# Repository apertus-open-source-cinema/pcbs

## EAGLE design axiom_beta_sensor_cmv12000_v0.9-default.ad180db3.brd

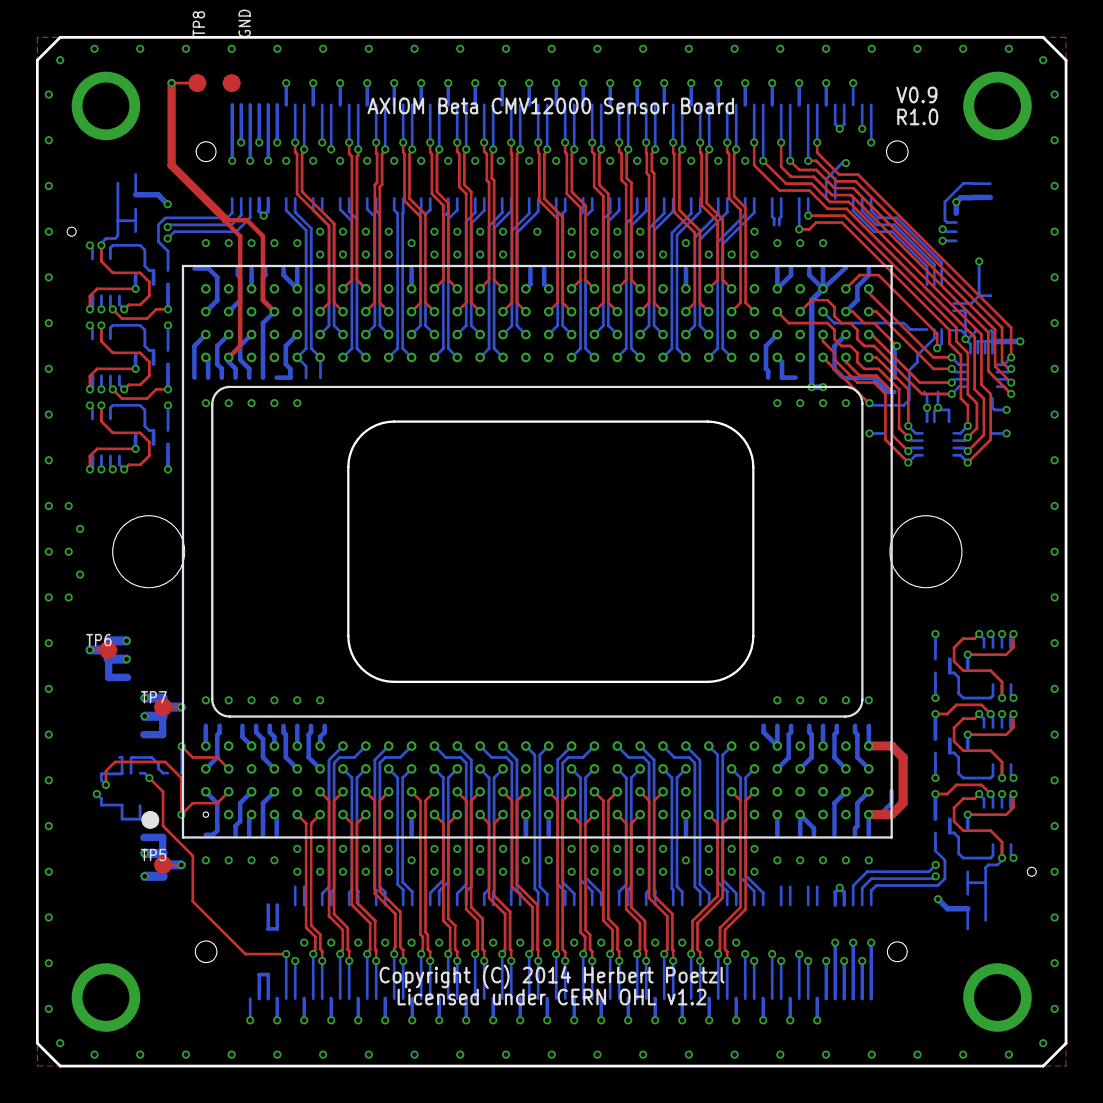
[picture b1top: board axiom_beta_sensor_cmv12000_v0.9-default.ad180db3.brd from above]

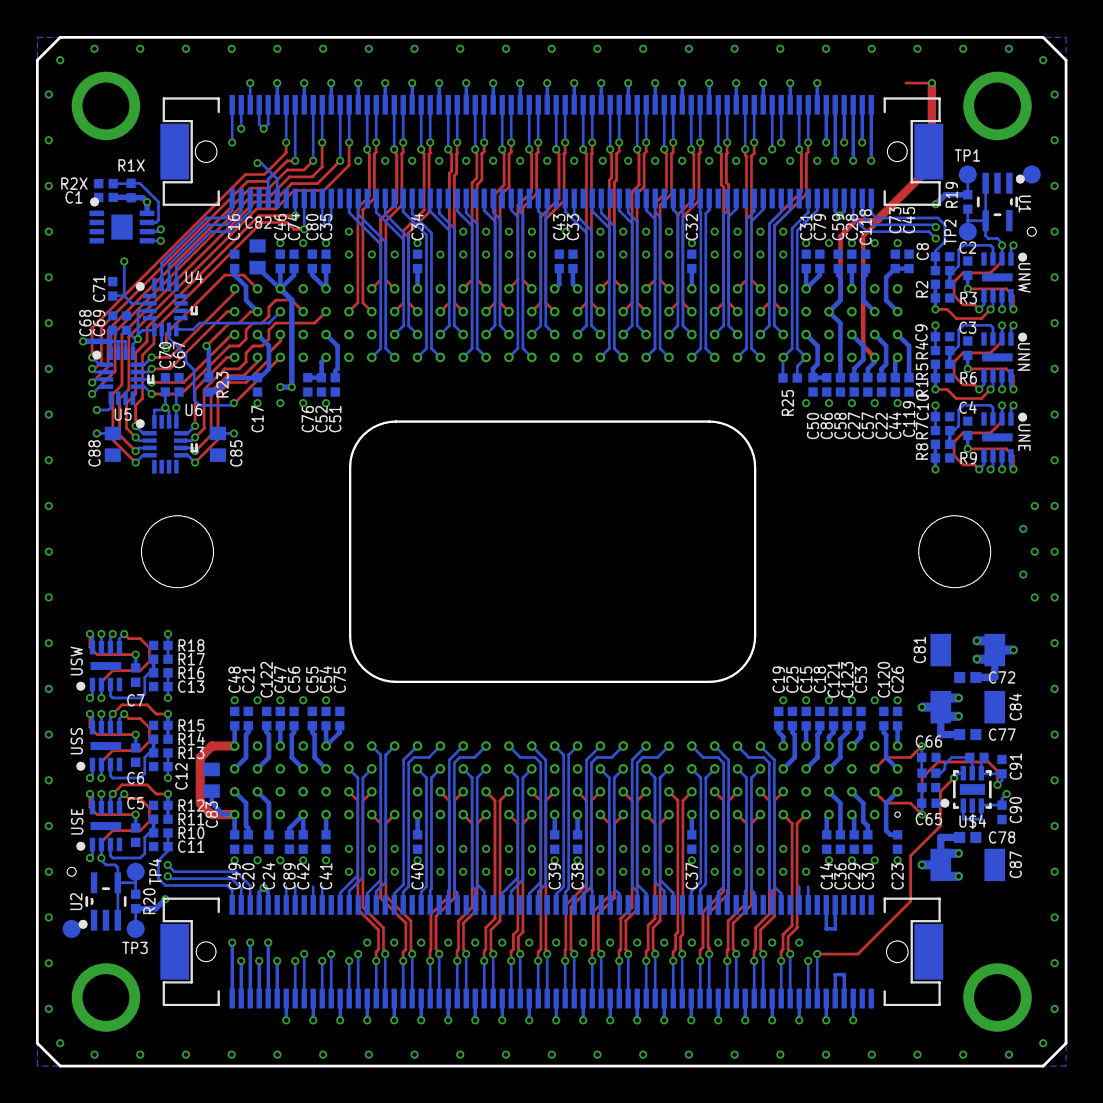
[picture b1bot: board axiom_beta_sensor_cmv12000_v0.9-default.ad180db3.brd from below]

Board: 4 copper layers, 57.1 x 57.1 mm, 148 parts (140 on the bottom side), 231 nets.

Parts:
C1, C2, C3, C4, C5, C6, C7, C14, C15, C16, C17, C18, C19, C20, C21, C22, C23, C24, C25, C26, C27, C28, C29, C30, C31, C32, C33, C34, C35, C36, C37, C38, C39, C40, C41, C42, C43, C44, C45, C46, C47, C48, C49, C50, C51, C52, C53, C54, C55, C56, C57, C58, C65, C66, C67, C68, C69, C70, C71, C118, C119, C120, C121, C122, C123: 100n; 0402-C
C8, C9, C10, C11, C12, C13: 1µ; 0402-C
C59, C73, C74, C75, C76, C79, C80, C86, C89, C90, C91: 4µ7; 0402-C
C72, C77, C78: 4µ7; 0402-B
C81, C84, C87: 100µ; 1206-B
C82, C83, C85, C88: 10µ; 0603-C
GND, GND75, GND77: TPTP10R; TP10R
PARALLELLA: PARALLELLA-FRAME
R1, R1X, R2, R2X, R3, R4, R5, R6, R7, R8, R9, R10, R11, R12, R13, R14, R15, R16, R17, R18, R19, R20, R21, R22, R23, R24, R25: 0402-C
TP1, TP2, TP3, TP4, TP5, TP6, TP7, TP8: TPTP10R; TP10R
U1, U2: TLV431ACDCKR; SOT65P210X110-5N
U4: SN74AVC4T245RSV; QFN40P185X265X55-16N
U5, U6: SN74AVC4T774RSV; QFN40P185X265X55-16N
U$1: µZ-FRAME
U$2: CMV12000ANDON; 10-30-07-237-400T4
U$4: MIC47050; MLF-6
UEP: BR24G04NUX; DFN200X300X100-9N
UNE: TS332IQ2T; DFN200X200X100-9N
UNN: TS332IQ2T; DFN200X200X100-9N
UNW: TS332IQ2T; DFN200X200X100-9N
USE: TS332IQ2T; DFN200X200X100-9N
USS: TS332IQ2T; DFN200X200X100-9N
USW: TS332IQ2T; DFN200X200X100-9N
X-NORTH: FX10-144P; FX10A-144P
X-SOUTH: FX10-144P; FX10A-144P

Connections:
CLK_IN: U6.12, U$2.E30
FRAME_REQ: U5.11, U$2.G30
GND: C1.2, C2.2, C3.2, C4.2, C5.2, C6.2, C7.2, C8.2, C9.2, C10.2, C11.2, C12.2, C13.2, C14.2, C15.2, C16.2, C17.2, C18.2, C19.2, C20.2, C21.2, C22.1, C23.1, C24.1, C25.1, C26.1, C27.1, C28.1, C29.2, C30.2, C31.2, C32.2, C33.2, C34.2, C35.2, C36.2, C37.2, C38.2, C39.2, C40.2, C41.2, C42.2, C43.2, C44.2, C45.2, C46.2, C47.2, C48.2, C49.2, C50.2, C51.2, C52.2, C53.2, C54.2, C55.2, C56.2, C57.2, C58.2, C59.2, C65.2, C66.2, C67.2, C68.2, C69.2, C70.2, C71.2, C72.2, C73.2, C74.2, C75.2, C76.2, C77.2, C78.2, C79.2, C80.2, C81.2, C82.2, C83.2, C84.2, C85.2, C86.2, C87.2, C88.2, C89.2, C90.2, C91.1, C118.2, C119.2, C120.2, C121.2, C122.2, C123.2, GND.TP, GND75.TP, GND77.TP, R2X.2, R3.2, R6.2, R9.2, R12.2, R15.2, R18.2, R22.1, U1.5, U2.5, U4.1, U4.4, U4.9, U4.10, U4.11, U4.16, U5.6, U5.7, U5.8, U6.5, U6.6, U6.7, U6.8, U6.15, U$2.A9, U$2.A21, U$2.A25, U$2.A28, U$2.A29, U$2.B5, U$2.B22, U$2.B26, U$2.B27, U$2.B28, U$2.C15, U$2.C16, U$2.C28, U$2.D2, U$2.D25, U$2.D27, U$2.D29, U$2.E3, U$2.E15, U$2.E16, U$2.E25, U$2.E27, U$2.F27, U$2.G5, U$2.H1, U$2.H6, U$2.H9, U$2.H21, U$2.H25, U$2.H27, U$4.2, U$4.EP, UEP.1, UEP.2, UEP.3, UEP.4, UEP.EP, UNE.4, UNE.EP, UNN.4, UNN.EP, UNW.4, UNW.EP, USE.4, USE.EP, USS.4, USS.EP, USW.4, USW.EP, X-NORTH.12, X-NORTH.18, X-NORTH.24, X-NORTH.30, X-NORTH.36, X-NORTH.42, X-NORTH.48, X-NORTH.54, X-NORTH.60, X-NORTH.66, X-NORTH.72, X-NORTH.78, X-NORTH.84, X-NORTH.90, X-NORTH.96, X-NORTH.102, X-NORTH.108, X-NORTH.114, X-NORTH.120, X-NORTH.126, X-NORTH.132, X-NORTH.138, X-NORTH.139, X-SOUTH.12, X-SOUTH.18, X-SOUTH.24, X-SOUTH.30, X-SOUTH.36, X-SOUTH.42, X-SOUTH.48, X-SOUTH.54, X-SOUTH.60, X-SOUTH.66, X-SOUTH.72, X-SOUTH.78, X-SOUTH.84, X-SOUTH.90, X-SOUTH.96, X-SOUTH.102, X-SOUTH.108, X-SOUTH.114, X-SOUTH.120, X-SOUTH.126, X-SOUTH.132, X-SOUTH.138, X-SOUTH.139
N00_N: R25.2, U$2.E6, X-NORTH.16
N00_P: R25.1, U$2.E5, X-NORTH.14
N01_N: U$2.G7, X-NORTH.17
N01_P: U$2.G6, X-NORTH.15
N02_N: U$2.F7, X-NORTH.22
N02_P: U$2.F6, X-NORTH.20
N04_N: U$2.E8, X-NORTH.28
N04_P: U$2.E7, X-NORTH.26
N05_N: U$2.H8, X-NORTH.29
N05_P: U$2.H7, X-NORTH.27
N06_N: U$2.F9, X-NORTH.34
N06_P: U$2.F8, X-NORTH.32
N07_N: U$2.G9, X-NORTH.35
N07_P: U$2.G8, X-NORTH.33
N08_N: U$2.E10, X-NORTH.40
N08_P: U$2.E9, X-NORTH.38
N09_N: U$2.G11, X-NORTH.41
N09_P: U$2.G10, X-NORTH.39
N10_N: U$2.F11, X-NORTH.46
N10_P: U$2.F10, X-NORTH.44
N11_N: U$2.H12, X-NORTH.47
N11_P: U$2.H11, X-NORTH.45
N12_N: U$2.E12, X-NORTH.52
N12_P: U$2.E11, X-NORTH.50
N13_N: U$2.G13, X-NORTH.53
N13_P: U$2.G12, X-NORTH.51
N14_N: U$2.F13, X-NORTH.58
N14_P: U$2.F12, X-NORTH.56
N15_N: U$2.H14, X-NORTH.59
N15_P: U$2.H13, X-NORTH.57
N16_N: U$2.E14, X-NORTH.64
N16_P: U$2.E13, X-NORTH.62
N17_N: U$2.G15, X-NORTH.65
N17_P: U$2.G14, X-NORTH.63
N18_N: U$2.F15, X-NORTH.70
N18_P: U$2.F14, X-NORTH.68
N19_N: U$2.G17, X-NORTH.71
N19_P: U$2.G16, X-NORTH.69
N20_N: U$2.F17, X-NORTH.76
N20_P: U$2.F16, X-NORTH.74
N21_N: U$2.H18, X-NORTH.77
N21_P: U$2.H17, X-NORTH.75
N22_N: U$2.E18, X-NORTH.82
N22_P: U$2.E17, X-NORTH.80
N23_N: U$2.G19, X-NORTH.83
N23_P: U$2.G18, X-NORTH.81
N24_N: U$2.F19, X-NORTH.88
N24_P: U$2.F18, X-NORTH.86
N25_N: U$2.H20, X-NORTH.89
N25_P: U$2.H19, X-NORTH.87
N26_N: U$2.E20, X-NORTH.94
N26_P: U$2.E19, X-NORTH.92
N27_N: U$2.G21, X-NORTH.95
N27_P: U$2.G20, X-NORTH.93
N28_N: U$2.F21, X-NORTH.100
N28_P: U$2.F20, X-NORTH.98
N29_N: U$2.G23, X-NORTH.101
N29_P: U$2.G22, X-NORTH.99
N30_N: U$2.E22, X-NORTH.106
N30_P: U$2.E21, X-NORTH.104
N31_N: U$2.H24, X-NORTH.107
N31_P: U$2.H23, X-NORTH.105
N32_N: U$2.F23, X-NORTH.112
N32_P: U$2.F22, X-NORTH.110
N33_N: U$2.G25, X-NORTH.113
N33_P: U$2.G24, X-NORTH.111
N34_N: U$2.E24, X-NORTH.118
N34_P: U$2.E23, X-NORTH.116
N35_N: U6.4, X-NORTH.119
N35_P: U6.3, X-NORTH.117
N37_N: U5.3, X-NORTH.125
N37_P: U5.4, X-NORTH.123
N38_N: U6.2, X-NORTH.130
N38_P: U6.1, X-NORTH.128
N39_N: U5.1, X-NORTH.131
N39_P: U5.2, X-NORTH.129
unnamed: R1X.2, R2X.1, UEP.7
unnamed: C118.1, U$2.G2
unnamed: C119.1, U$2.F1
unnamed: C120.1, U$2.C1
unnamed: C121.1, U$2.D4
unnamed: C122.1, U$2.C29
unnamed: C123.1, U$2.C4
unnamed: C14.1, U$2.A4
unnamed: C15.1, U$2.D5
unnamed: R21.1, R22.2, U$4.5
unnamed: C18.1, U$2.C5
unnamed: C19.1, U$2.D6
unnamed: C20.1, U$2.B30
unnamed: C21.1, U$2.C30
unnamed: C22.2, U$2.F2
unnamed: C23.2, U$2.B1
unnamed: C24.2, U$2.B29
unnamed: C25.2, U$2.C6
unnamed: C26.2, U$2.D1
unnamed: C27.2, U$2.F3
unnamed: C28.2, U$2.H3
unnamed: C29.1, U$2.A3
unnamed: C30.1, U$2.B3
unnamed: R11.2, R12.1, USE.6
unnamed: R5.2, R6.1, UNN.6
unnamed: R8.2, R9.1, UNE.6
unnamed: R10.2, R11.1, USE.3
unnamed: R7.2, R8.1, UNE.3
unnamed: R1.2, R2.1, UNW.3
unnamed: R2.2, R3.1, UNW.6
unnamed: R14.2, R15.1, USS.6
unnamed: R13.2, R14.1, USS.3
unnamed: R16.2, R17.1, USW.3
unnamed: R17.2, R18.1, USW.6
N_CHK_V: C2.1, C3.1, C4.1, R19.1, TP1.TP, UNE.8, UNN.8, UNW.8, X-NORTH.8, X-NORTH.10
N_I2C_V: C1.1, R1X.1, UEP.8, X-NORTH.135, X-NORTH.137
N_REF: R19.2, TP2.TP, U1.3, U1.4, UNE.2, UNE.5, UNN.2, UNN.5, UNW.2, UNW.5
N_SCK: U4.15, X-NORTH.144
N_SCL: UEP.6, X-NORTH.143
N_SDA: UEP.5, X-NORTH.141
N_SDI: U4.13, X-NORTH.140
N_SDO: U4.14, X-NORTH.142
N_SPI_V: C71.1, U4.2, X-NORTH.134, X-NORTH.136
N_VE: C50.1, C51.1, C52.1, C53.1, C54.1, C55.1, C56.1, C67.1, C69.1, C75.1, C76.1, C77.1, C84.1, C85.1, C86.1, TP7.TP, U4.3, U4.5, U5.13, U6.13, U$2.C26, U$2.C27, U$2.D3, U$2.D26, U$2.E26, U$2.F5, U$2.F26, X-NORTH.103, X-NORTH.109, X-NORTH.115, X-NORTH.121, X-NORTH.127, X-NORTH.133
N_VE_CV: C10.1, R7.1, X-NORTH.6
N_VE_OV: UNE.7, X-NORTH.5
N_VE_UV: UNE.1, X-NORTH.11
N_VN: C31.1, C32.1, C33.1, C34.1, C35.1, C36.1, C37.1, C38.1, C39.1, C40.1, C41.1, C42.1, C43.1, C44.1, C68.1, C70.1, C78.1, C79.1, C80.1, C87.1, C88.1, C89.1, TP5.TP, U5.5, U5.14, U5.15, U5.16, U6.14, U6.16, U$2.A10, U$2.A15, U$2.A16, U$2.A22, U$2.A26, U$2.A27, U$2.B4, U$2.E1, U$2.H5, U$2.H10, U$2.H15, U$2.H16, U$2.H22, U$2.H26, X-NORTH.49, X-NORTH.55, X-NORTH.61, X-NORTH.67, X-NORTH.73, X-NORTH.79, X-NORTH.85, X-NORTH.91, X-NORTH.97
N_VN_CV: C9.1, R4.1, X-NORTH.4
N_VN_OV: UNN.7, X-NORTH.3
N_VN_UV: UNN.1, X-NORTH.9
N_VW: C57.1, C58.1, C59.1, TP8.TP, U$2.E2, U$2.G4, X-NORTH.13, X-NORTH.19, X-NORTH.25, X-NORTH.31, X-NORTH.37, X-NORTH.43
N_VW_CV: C8.1, R1.1, X-NORTH.2
N_VW_OV: UNW.7, X-NORTH.1
N_VW_UV: UNW.1, X-NORTH.7
R5: R4.2, R5.1, UNN.3
S04_N: U$2.C24, X-SOUTH.28
S04_P: U$2.C25, X-SOUTH.26
S06_N: U$2.D23, X-SOUTH.34
S06_P: U$2.D24, X-SOUTH.32
S07_N: U$2.B24, X-SOUTH.35
S07_P: U$2.B25, X-SOUTH.33
S08_N: U$2.D21, X-SOUTH.40
S08_P: U$2.D22, X-SOUTH.38
S09_N: U$2.A23, X-SOUTH.41
S09_P: U$2.A24, X-SOUTH.39
S10_N: U$2.C21, X-SOUTH.46
S10_P: U$2.C22, X-SOUTH.44
S11_N: U$2.B20, X-SOUTH.47
S11_P: U$2.B21, X-SOUTH.45
S12_N: U$2.D19, X-SOUTH.52
S12_P: U$2.D20, X-SOUTH.50
S13_N: U$2.A19, X-SOUTH.53
S13_P: U$2.A20, X-SOUTH.51
S14_N: U$2.C19, X-SOUTH.58
S14_P: U$2.C20, X-SOUTH.56
S15_N: U$2.B18, X-SOUTH.59
S15_P: U$2.B19, X-SOUTH.57
S16_N: U$2.C17, X-SOUTH.64
S16_P: U$2.C18, X-SOUTH.62
S17_N: U$2.A17, X-SOUTH.65
S17_P: U$2.A18, X-SOUTH.63
S18_N: U$2.D17, X-SOUTH.70
S18_P: U$2.D18, X-SOUTH.68
S19_N: U$2.B16, X-SOUTH.71
S19_P: U$2.B17, X-SOUTH.69
S20_N: U$2.D15, X-SOUTH.76
S20_P: U$2.D16, X-SOUTH.74
S21_N: U$2.B14, X-SOUTH.77
S21_P: U$2.B15, X-SOUTH.75
S22_N: U$2.D13, X-SOUTH.82
S22_P: U$2.D14, X-SOUTH.80
S23_N: U$2.A13, X-SOUTH.83
S23_P: U$2.A14, X-SOUTH.81
S24_N: U$2.C13, X-SOUTH.88
S24_P: U$2.C14, X-SOUTH.86
S25_N: U$2.B12, X-SOUTH.89
S25_P: U$2.B13, X-SOUTH.87
S26_N: U$2.D11, X-SOUTH.94
S26_P: U$2.D12, X-SOUTH.92
S27_N: U$2.A11, X-SOUTH.95
S27_P: U$2.A12, X-SOUTH.93
S28_N: U$2.C11, X-SOUTH.100
S28_P: U$2.C12, X-SOUTH.98
S29_N: U$2.B10, X-SOUTH.101
S29_P: U$2.B11, X-SOUTH.99
S30_N: U$2.C9, X-SOUTH.106
S30_P: U$2.C10, X-SOUTH.104
S31_N: U$2.B8, X-SOUTH.107
S31_P: U$2.B9, X-SOUTH.105
S32_N: U$2.D9, X-SOUTH.112
S32_P: U$2.D10, X-SOUTH.110
S33_N: U$2.A7, X-SOUTH.113
S33_P: U$2.A8, X-SOUTH.111
S34_N: U$2.C7, X-SOUTH.118
S34_P: U$2.C8, X-SOUTH.116
S35_N: U$2.B6, X-SOUTH.119
S35_P: U$2.B7, X-SOUTH.117
S36_N: U$2.D7, X-SOUTH.124
S36_P: U$2.D8, X-SOUTH.122
S37_N: U$2.A5, X-SOUTH.125
S37_P: U$2.A6, X-SOUTH.123
S39_N: U$4.6, X-SOUTH.131
SPI_CLK: U4.6, U$2.H29
SPI_EN: U6.9, U$2.F28
SPI_IN: U4.7, U$2.E28
SPI_OUT: U4.8, U$2.G28
SYS_RES_N: U5.10, U$2.F30
S_CHK_V: C5.1, C6.1, C7.1, R20.1, TP3.TP, USE.8, USS.8, USW.8, X-SOUTH.8, X-SOUTH.10
S_I2C_V: X-SOUTH.135, X-SOUTH.137
S_REF: R20.2, TP4.TP, U2.3, U2.4, USE.2, USE.5, USS.2, USS.5, USW.2, USW.5
S_SPI_V: X-SOUTH.134, X-SOUTH.136
S_VE: X-SOUTH.13, X-SOUTH.19, X-SOUTH.25, X-SOUTH.31, X-SOUTH.37, X-SOUTH.43
S_VE_CV: C11.1, R10.1, X-SOUTH.2
S_VE_OV: USE.7, X-SOUTH.1
S_VE_UV: USE.1, X-SOUTH.7
S_VS: C45.1, C46.1, C47.1, C48.1, C49.1, C72.1, C73.1, C74.1, C81.1, C82.1, C83.1, TP6.TP, U$2.A30, U$2.D28, U$2.D30, U$2.G1, U$2.H28, X-SOUTH.49, X-SOUTH.55, X-SOUTH.61, X-SOUTH.67, X-SOUTH.73, X-SOUTH.79, X-SOUTH.85, X-SOUTH.91, X-SOUTH.97
S_VS_CV: C12.1, R13.1, X-SOUTH.4
S_VS_OV: USS.7, X-SOUTH.3
S_VS_UV: USS.1, X-SOUTH.9
S_VW: C90.1, U$4.1, U$4.3, X-SOUTH.103, X-SOUTH.109, X-SOUTH.115, X-SOUTH.121, X-SOUTH.127, X-SOUTH.133
S_VW_CV: C13.1, R16.1, X-SOUTH.6
S_VW_OV: USW.7, X-SOUTH.5
S_VW_UV: USW.1, X-SOUTH.11
TDIG1: U5.9, U$2.G27
TDIG2: U6.11, U$2.G26
T_EXP1: U5.12, U$2.H30
T_EXP2: U6.10, U$2.E29
VRAMP1: C16.1, R23.1, U$2.G29
VRAMP2: C17.1, R23.2, U$2.F29
VTREF: C65.1, C91.2, R21.2, R24.1, U$2.B2, U$4.4
VTSIG: C66.1, R24.2, U$2.C2

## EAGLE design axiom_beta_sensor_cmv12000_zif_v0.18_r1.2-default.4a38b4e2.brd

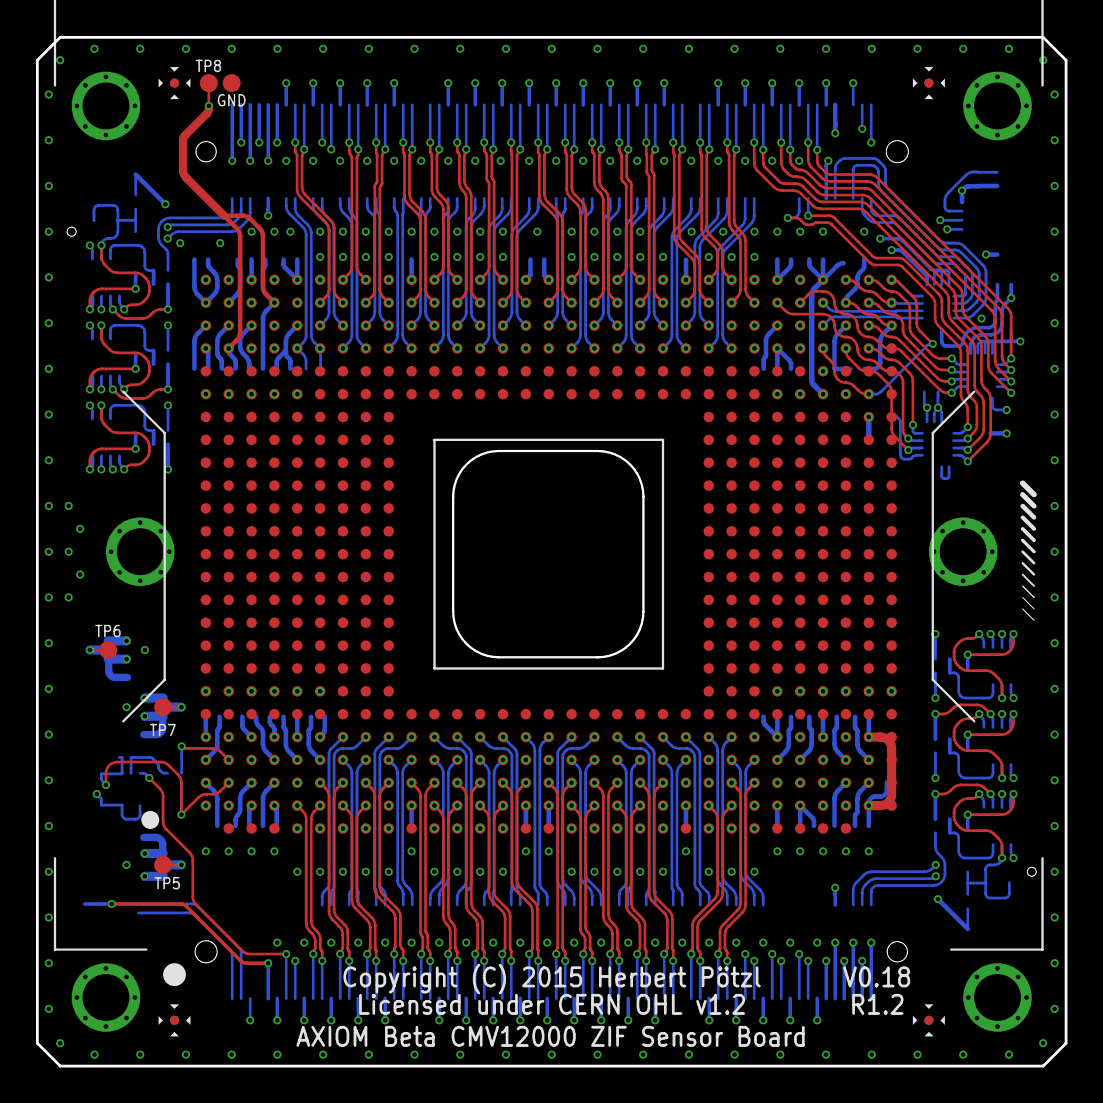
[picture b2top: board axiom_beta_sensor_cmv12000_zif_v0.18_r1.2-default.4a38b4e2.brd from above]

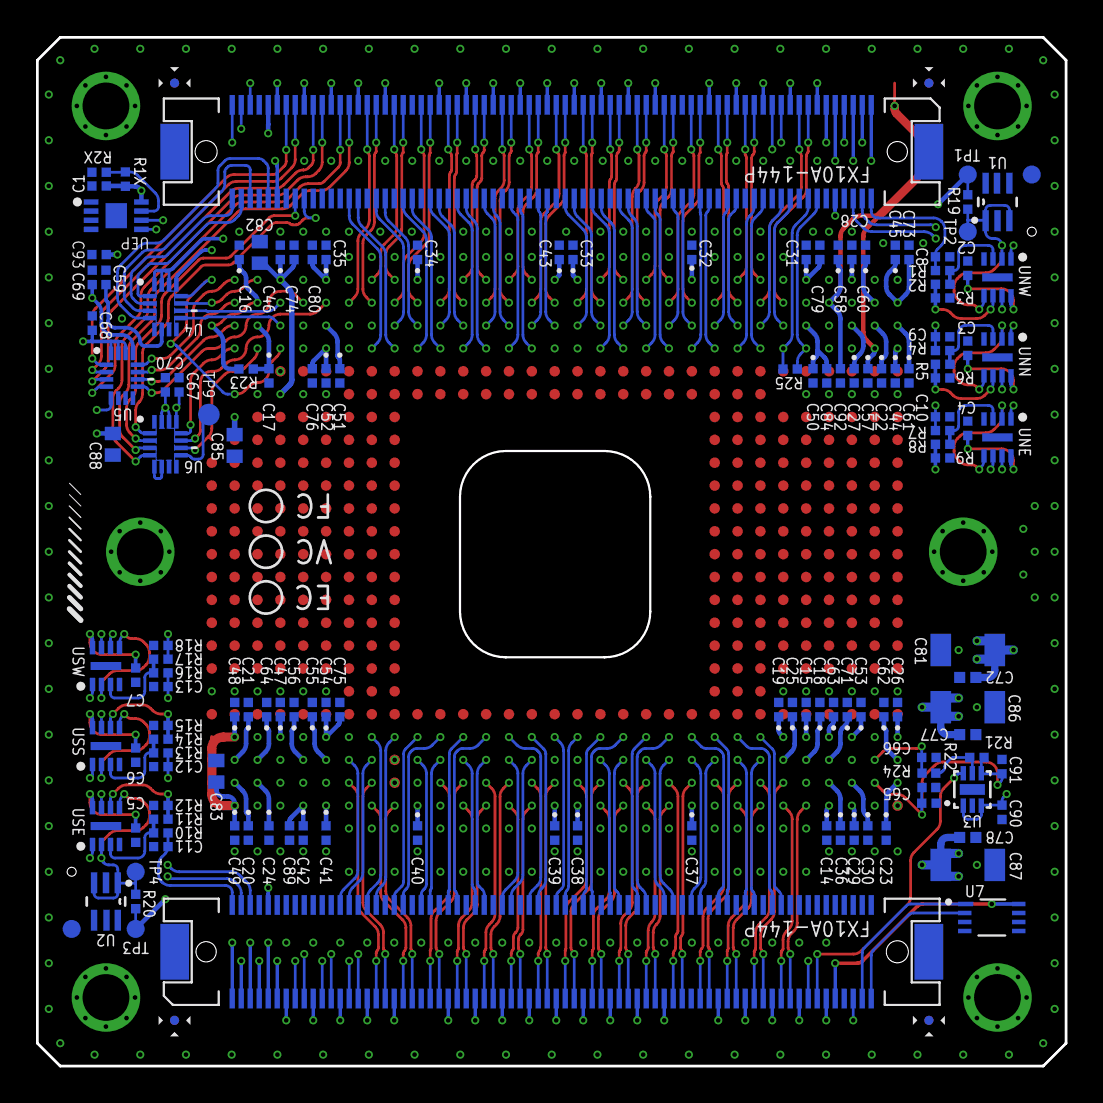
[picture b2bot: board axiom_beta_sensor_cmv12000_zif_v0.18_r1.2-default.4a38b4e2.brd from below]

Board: 4 copper layers, 57.1 x 57.1 mm, 151 parts (143 on the bottom side), 234 nets.

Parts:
C1, C2, C3, C4, C5, C6, C7, C14, C15, C16, C17, C18, C19, C20, C21, C22, C23, C24, C25, C26, C27, C28, C29, C30, C31, C32, C33, C34, C35, C36, C37, C38, C39, C40, C41, C42, C43, C44, C45, C46, C47, C48, C49, C50, C51, C52, C53, C54, C55, C56, C57, C58, C59, C60, C61, C62, C63, C64, C65, C66, C67, C68, C69, C70, C71, C93: 100n; 0402-C
C8, C9, C10, C11, C12, C13: 1µ; 0402-C
C72, C77, C78: 4µ7; 0402-B
C73, C74, C75, C76, C79, C80, C84, C89, C90, C91, C92: 4µ7; 0402-C
C81, C86, C87: 100µ; 1206-B
C82, C83, C85, C88: 10µ; 0603-C
GND, GND75, GND77: TPTP10R; TP10R
PARALLELLA: PARALLELLA-FRAME
R1, R7: 28k7; 0402-C
R1X: 10k; 0402-C
R2, R8: 3k32; 0402-C
R2X, R10, R11, R12: 0402-C
R3, R9, R15, R18: 16k9; 0402-C
R4: 15k4; 0402-C
R5: 3k09; 0402-C
R6: 30k9; 0402-C
R13: 22k6; 0402-C
R14: 9k53; 0402-C
R16: 18k7; 0402-C
R17: 13k3; 0402-C
R19, R20: 18k; 0402-C
R21: 5k9; 0402-C
R22: 14k3; 0402-C
R23, R24: 0R; 0402-C
R25: 100R; 0402-C
SENSOR: CMV12000-ZIF; ZIF-604
TP1, TP2, TP3, TP4, TP5, TP6, TP7, TP8: TPTP10R; TP10R
TP9: TPTP12R; TP12R
U1, U2: TLV431DCK; SOT65P210X110-6N
U3: MIC47050; MLF-6
U4, U5, U6: SN74AVC4T774RSV; QFN40P185X265X55-16N
U7: LM75BGD; SOT996-2/3
U$1: µZ-FRAME
UEP: BR24G04NUX; DFN200X300X100-9N
UNE: TS332IQ2T; DFN200X200X100-9N
UNN: TS332IQ2T; DFN200X200X100-9N
UNW: TS332IQ2T; DFN200X200X100-9N
USE: TS332IQ2T; DFN200X200X100-9N
USS: TS332IQ2T; DFN200X200X100-9N
USW: TS332IQ2T; DFN200X200X100-9N
X-NORTH: FX10-144P; FX10A-144P
X-SOUTH: FX10-144P; FX10A-144P

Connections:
CLK_IN: SENSOR.E30, U6.12
FRAME_REQ: SENSOR.G30, U5.11
GND: C1.2, C2.2, C3.2, C4.2, C5.2, C6.2, C7.2, C8.2, C9.2, C10.2, C11.2, C12.2, C13.2, C14.2, C15.2, C16.2, C17.2, C18.2, C19.2, C20.2, C21.2, C22.1, C23.1, C24.1, C25.1, C26.1, C27.1, C28.1, C29.2, C30.2, C31.2, C32.2, C33.2, C34.2, C35.2, C36.2, C37.2, C38.2, C39.2, C40.2, C41.2, C42.2, C43.2, C44.2, C45.2, C46.2, C47.2, C48.2, C49.2, C50.2, C51.2, C52.2, C53.2, C54.2, C55.2, C56.2, C57.2, C58.2, C59.2, C60.2, C61.2, C62.2, C63.2, C64.2, C65.2, C66.2, C67.2, C68.2, C69.2, C70.2, C71.2, C72.2, C73.2, C74.2, C75.2, C76.2, C77.2, C78.2, C79.2, C80.2, C81.2, C82.2, C83.2, C84.2, C85.2, C86.2, C87.2, C88.2, C89.2, C90.2, C91.1, C92.2, C93.2, GND.TP, GND75.TP, GND77.TP, R2X.2, R3.2, R6.2, R9.2, R12.2, R15.2, R18.2, R22.1, SENSOR.A9, SENSOR.A21, SENSOR.A25, SENSOR.A28, SENSOR.A29, SENSOR.B5, SENSOR.B22, SENSOR.B26, SENSOR.B27, SENSOR.B28, SENSOR.C15, SENSOR.C16, SENSOR.C28, SENSOR.D2, SENSOR.D25, SENSOR.D27, SENSOR.D29, SENSOR.E3, SENSOR.E15, SENSOR.E16, SENSOR.E25, SENSOR.E27, SENSOR.F27, SENSOR.G5, SENSOR.H1, SENSOR.H6, SENSOR.H9, SENSOR.H21, SENSOR.H25, SENSOR.H27, SENSOR.X2, SENSOR.X3, SENSOR.X4, SENSOR.X5, SENSOR.X6, SENSOR.X7, SENSOR.X8, SENSOR.X9, SENSOR.X10, SENSOR.X11, SENSOR.X12, SENSOR.X13, SENSOR.X14, SENSOR.X15, SENSOR.X16, SENSOR.X17, SENSOR.X18, SENSOR.X19, SENSOR.X20, SENSOR.X21, SENSOR.X22, SENSOR.X23, SENSOR.X24, SENSOR.X25, SENSOR.X26, SENSOR.X27, SENSOR.X28, SENSOR.X29, SENSOR.Y1, SENSOR.Y2, SENSOR.Y3, SENSOR.Y4, SENSOR.Y5, SENSOR.Y6, SENSOR.Y7, SENSOR.Y8, SENSOR.Y9, SENSOR.Y10, SENSOR.Y11, SENSOR.Y12, SENSOR.Y13, SENSOR.Y14, SENSOR.Y15, SENSOR.Y16, SENSOR.Y17, SENSOR.Y18, SENSOR.Y19, SENSOR.Y20, SENSOR.Y22, SENSOR.Z14, U1.6, U2.6, U3.2, U3.EP, U4.5, U4.7, U4.8, U5.6, U5.7, U5.8, U6.7, U6.8, U6.16, U7.4, U7.5, U7.6, U7.7, UEP.1, UEP.2, UEP.3, UEP.4, UEP.EP, UNE.4, UNE.EP, UNN.4, UNN.EP, UNW.4, UNW.EP, USE.4, USE.EP, USS.4, USS.EP, USW.4, USW.EP, X-NORTH.12, X-NORTH.18, X-NORTH.24, X-NORTH.30, X-NORTH.36, X-NORTH.42, X-NORTH.43, X-NORTH.48, X-NORTH.54, X-NORTH.60, X-NORTH.66, X-NORTH.72, X-NORTH.78, X-NORTH.84, X-NORTH.90, X-NORTH.96, X-NORTH.102, X-NORTH.103, X-NORTH.108, X-NORTH.114, X-NORTH.120, X-NORTH.126, X-NORTH.132, X-NORTH.138, X-NORTH.139, X-SOUTH.12, X-SOUTH.18, X-SOUTH.24, X-SOUTH.30, X-SOUTH.36, X-SOUTH.42, X-SOUTH.43, X-SOUTH.48, X-SOUTH.54, X-SOUTH.60, X-SOUTH.66, X-SOUTH.72, X-SOUTH.78, X-SOUTH.84, X-SOUTH.90, X-SOUTH.96, X-SOUTH.102, X-SOUTH.103, X-SOUTH.108, X-SOUTH.114, X-SOUTH.120, X-SOUTH.126, X-SOUTH.132, X-SOUTH.138, X-SOUTH.139
N00_N: R25.2, SENSOR.E6, X-NORTH.16
N00_P: R25.1, SENSOR.E5, X-NORTH.14
N01_N: SENSOR.G7, X-NORTH.17
N01_P: SENSOR.G6, X-NORTH.15
N02_N: SENSOR.F7, X-NORTH.22
N02_P: SENSOR.F6, X-NORTH.20
N04_N: SENSOR.E8, X-NORTH.28
N04_P: SENSOR.E7, X-NORTH.26
N05_N: SENSOR.H8, X-NORTH.29
N05_P: SENSOR.H7, X-NORTH.27
N06_N: SENSOR.F9, X-NORTH.34
N06_P: SENSOR.F8, X-NORTH.32
N07_N: SENSOR.G9, X-NORTH.35
N07_P: SENSOR.G8, X-NORTH.33
N08_N: SENSOR.E10, X-NORTH.40
N08_P: SENSOR.E9, X-NORTH.38
N09_N: SENSOR.G11, X-NORTH.41
N09_P: SENSOR.G10, X-NORTH.39
N10_N: SENSOR.F11, X-NORTH.46
N10_P: SENSOR.F10, X-NORTH.44
N11_N: SENSOR.H12, X-NORTH.47
N11_P: SENSOR.H11, X-NORTH.45
N12_N: SENSOR.E12, X-NORTH.52
N12_P: SENSOR.E11, X-NORTH.50
N13_N: SENSOR.G13, X-NORTH.53
N13_P: SENSOR.G12, X-NORTH.51
N14_N: SENSOR.F13, X-NORTH.58
N14_P: SENSOR.F12, X-NORTH.56
N15_N: SENSOR.H14, X-NORTH.59
N15_P: SENSOR.H13, X-NORTH.57
N16_N: SENSOR.E14, X-NORTH.64
N16_P: SENSOR.E13, X-NORTH.62
N17_N: SENSOR.G15, X-NORTH.65
N17_P: SENSOR.G14, X-NORTH.63
N18_N: SENSOR.F15, X-NORTH.70
N18_P: SENSOR.F14, X-NORTH.68
N19_N: SENSOR.G17, X-NORTH.71
N19_P: SENSOR.G16, X-NORTH.69
N20_N: SENSOR.F17, X-NORTH.76
N20_P: SENSOR.F16, X-NORTH.74
N21_N: SENSOR.H18, X-NORTH.77
N21_P: SENSOR.H17, X-NORTH.75
N22_N: SENSOR.E18, X-NORTH.82
N22_P: SENSOR.E17, X-NORTH.80
N23_N: SENSOR.G19, X-NORTH.83
N23_P: SENSOR.G18, X-NORTH.81
N24_N: SENSOR.F19, X-NORTH.88
N24_P: SENSOR.F18, X-NORTH.86
N25_N: SENSOR.H20, X-NORTH.89
N25_P: SENSOR.H19, X-NORTH.87
N26_N: SENSOR.E20, X-NORTH.94
N26_P: SENSOR.E19, X-NORTH.92
N27_N: SENSOR.G21, X-NORTH.95
N27_P: SENSOR.G20, X-NORTH.93
N28_N: SENSOR.F21, X-NORTH.100
N28_P: SENSOR.F20, X-NORTH.98
N29_N: SENSOR.G23, X-NORTH.101
N29_P: SENSOR.G22, X-NORTH.99
N30_N: SENSOR.E22, X-NORTH.106
N30_P: SENSOR.E21, X-NORTH.104
N31_N: SENSOR.H24, X-NORTH.107
N31_P: SENSOR.H23, X-NORTH.105
N32_N: SENSOR.F23, X-NORTH.112
N32_P: SENSOR.F22, X-NORTH.110
N33_N: SENSOR.G25, X-NORTH.113
N33_P: SENSOR.G24, X-NORTH.111
N34_N: SENSOR.E24, X-NORTH.118
N34_P: SENSOR.E23, X-NORTH.116
N35_N: U6.4, X-NORTH.119
N35_P: U6.3, X-NORTH.117
N37_N: U5.3, X-NORTH.125
N37_P: U5.4, X-NORTH.123
N38_N: U6.2, X-NORTH.130
N38_P: U6.1, X-NORTH.128
N39_N: U5.1, X-NORTH.131
N39_P: U5.2, X-NORTH.129
unnamed: R1X.2, R2X.1, UEP.7
unnamed: C60.1, SENSOR.G2
unnamed: C61.1, SENSOR.F1
unnamed: C62.1, SENSOR.C1
unnamed: C63.1, SENSOR.D4
unnamed: C64.1, SENSOR.C29
unnamed: C71.1, SENSOR.C4
unnamed: C14.1, SENSOR.A4
unnamed: C15.1, SENSOR.D5
unnamed: R21.1, R22.2, U3.5
unnamed: C18.1, SENSOR.C5
unnamed: C19.1, SENSOR.D6
unnamed: C20.1, SENSOR.B30
unnamed: C21.1, SENSOR.C30
unnamed: C22.2, SENSOR.F2
unnamed: C23.2, SENSOR.B1
unnamed: C24.2, SENSOR.B29
unnamed: C25.2, SENSOR.C6
unnamed: C26.2, SENSOR.D1
unnamed: C27.2, SENSOR.F3
unnamed: C28.2, SENSOR.H3
unnamed: C29.1, SENSOR.A3
unnamed: C30.1, SENSOR.B3
unnamed: TP9.TP, U6.9
unnamed: R11.2, R12.1, USE.6
unnamed: R5.2, R6.1, UNN.6
unnamed: R8.2, R9.1, UNE.6
unnamed: R10.2, R11.1, USE.3
unnamed: R7.2, R8.1, UNE.3
unnamed: R1.2, R2.1, UNW.3
unnamed: R2.2, R3.1, UNW.6
unnamed: R14.2, R15.1, USS.6
unnamed: R13.2, R14.1, USS.3
unnamed: R16.2, R17.1, USW.3
unnamed: R17.2, R18.1, USW.6
N_CHK_V: C2.1, C3.1, C4.1, R19.1, TP1.TP, UNE.8, UNN.8, UNW.8, X-NORTH.10
N_I2C_V: C1.1, R1X.1, UEP.8, X-NORTH.135
N_REF: R19.2, TP2.TP, U1.1, U1.3, UNE.2, UNE.5, UNN.2, UNN.5, UNW.2, UNW.5
N_SCK: U4.2, X-NORTH.144
N_SCL: UEP.6, X-NORTH.143
N_SDA: UEP.5, X-NORTH.141
N_SDI: U4.3, X-NORTH.140
N_SDO: U4.1, X-NORTH.142
N_SPI_EN: U4.4, X-NORTH.136
N_SPI_V: C59.1, U4.6, U4.14, U4.15, U4.16, X-NORTH.134
N_VE: C50.1, C51.1, C52.1, C53.1, C54.1, C55.1, C56.1, C67.1, C69.1, C75.1, C76.1, C77.1, C84.1, C85.1, C86.1, C93.1, SENSOR.C26, SENSOR.C27, SENSOR.D3, SENSOR.D26, SENSOR.E26, SENSOR.F5, SENSOR.F26, SENSOR.Z12, TP7.TP, U4.13, U5.13, U6.13, X-NORTH.109, X-NORTH.115, X-NORTH.121, X-NORTH.127, X-NORTH.133
N_VE_CV: C10.1, R7.1, X-NORTH.6
N_VE_OV: UNE.7, X-NORTH.5
N_VE_UV: UNE.1, X-NORTH.11
N_VN: C31.1, C32.1, C33.1, C34.1, C35.1, C36.1, C37.1, C38.1, C39.1, C40.1, C41.1, C42.1, C43.1, C44.1, C68.1, C70.1, C78.1, C79.1, C80.1, C87.1, C88.1, C89.1, SENSOR.A10, SENSOR.A15, SENSOR.A16, SENSOR.A22, SENSOR.A26, SENSOR.A27, SENSOR.B4, SENSOR.E1, SENSOR.H5, SENSOR.H10, SENSOR.H15, SENSOR.H16, SENSOR.H22, SENSOR.H26, TP5.TP, U5.5, U5.14, U5.15, U5.16, U6.5, U6.6, U6.14, U6.15, X-NORTH.49, X-NORTH.55, X-NORTH.61, X-NORTH.67, X-NORTH.73, X-NORTH.79, X-NORTH.85, X-NORTH.91, X-NORTH.97
N_VN_CV: C9.1, R4.1, X-NORTH.4
N_VN_OV: UNN.7, X-NORTH.3
N_VN_UV: UNN.1, X-NORTH.9
N_VW: C57.1, C58.1, C92.1, SENSOR.E2, SENSOR.G4, TP8.TP, X-NORTH.13, X-NORTH.19, X-NORTH.25, X-NORTH.31, X-NORTH.37
N_VW_CV: C8.1, R1.1, X-NORTH.2
N_VW_OV: UNW.7, X-NORTH.1
N_VW_UV: UNW.1, X-NORTH.7
R5: R4.2, R5.1, UNN.3
S04_N: SENSOR.C24, X-SOUTH.28
S04_P: SENSOR.C25, X-SOUTH.26
S06_N: SENSOR.D23, X-SOUTH.34
S06_P: SENSOR.D24, X-SOUTH.32
S07_N: SENSOR.B24, X-SOUTH.35
S07_P: SENSOR.B25, X-SOUTH.33
S08_N: SENSOR.D21, X-SOUTH.40
S08_P: SENSOR.D22, X-SOUTH.38
S09_N: SENSOR.A23, X-SOUTH.41
S09_P: SENSOR.A24, X-SOUTH.39
S10_N: SENSOR.C21, X-SOUTH.46
S10_P: SENSOR.C22, X-SOUTH.44
S11_N: SENSOR.B20, X-SOUTH.47
S11_P: SENSOR.B21, X-SOUTH.45
S12_N: SENSOR.D19, X-SOUTH.52
S12_P: SENSOR.D20, X-SOUTH.50
S13_N: SENSOR.A19, X-SOUTH.53
S13_P: SENSOR.A20, X-SOUTH.51
S14_N: SENSOR.C19, X-SOUTH.58
S14_P: SENSOR.C20, X-SOUTH.56
S15_N: SENSOR.B18, X-SOUTH.59
S15_P: SENSOR.B19, X-SOUTH.57
S16_N: SENSOR.C17, X-SOUTH.64
S16_P: SENSOR.C18, X-SOUTH.62
S17_N: SENSOR.A17, X-SOUTH.65
S17_P: SENSOR.A18, X-SOUTH.63
S18_N: SENSOR.D17, X-SOUTH.70
S18_P: SENSOR.D18, X-SOUTH.68
S19_N: SENSOR.B16, X-SOUTH.71
S19_P: SENSOR.B17, X-SOUTH.69
S20_N: SENSOR.D15, X-SOUTH.76
S20_P: SENSOR.D16, X-SOUTH.74
S21_N: SENSOR.B14, X-SOUTH.77
S21_P: SENSOR.B15, X-SOUTH.75
S22_N: SENSOR.D13, X-SOUTH.82
S22_P: SENSOR.D14, X-SOUTH.80
S23_N: SENSOR.A13, X-SOUTH.83
S23_P: SENSOR.A14, X-SOUTH.81
S24_N: SENSOR.C13, X-SOUTH.88
S24_P: SENSOR.C14, X-SOUTH.86
S25_N: SENSOR.B12, X-SOUTH.89
S25_P: SENSOR.B13, X-SOUTH.87
S26_N: SENSOR.D11, X-SOUTH.94
S26_P: SENSOR.D12, X-SOUTH.92
S27_N: SENSOR.A11, X-SOUTH.95
S27_P: SENSOR.A12, X-SOUTH.93
S28_N: SENSOR.C11, X-SOUTH.100
S28_P: SENSOR.C12, X-SOUTH.98
S29_N: SENSOR.B10, X-SOUTH.101
S29_P: SENSOR.B11, X-SOUTH.99
S30_N: SENSOR.C9, X-SOUTH.106
S30_P: SENSOR.C10, X-SOUTH.104
S31_N: SENSOR.B8, X-SOUTH.107
S31_P: SENSOR.B9, X-SOUTH.105
S32_N: SENSOR.D9, X-SOUTH.112
S32_P: SENSOR.D10, X-SOUTH.110
S33_N: SENSOR.A7, X-SOUTH.113
S33_P: SENSOR.A8, X-SOUTH.111
S34_N: SENSOR.C7, X-SOUTH.118
S34_P: SENSOR.C8, X-SOUTH.116
S35_N: SENSOR.B6, X-SOUTH.119
S35_P: SENSOR.B7, X-SOUTH.117
S36_N: SENSOR.D7, X-SOUTH.124
S36_P: SENSOR.D8, X-SOUTH.122
S37_N: SENSOR.A5, X-SOUTH.125
S37_P: SENSOR.A6, X-SOUTH.123
S39_N: U3.6, X-SOUTH.131
SPI_CLK: SENSOR.H29, SENSOR.Z10, U4.11
SPI_EN: SENSOR.F28, U4.9
SPI_IN: SENSOR.E28, SENSOR.Y23, SENSOR.Z11, U4.12
SPI_OUT: SENSOR.G28, U4.10
SYS_RES_N: SENSOR.F30, U5.10
S_CHK_V: C5.1, C6.1, C7.1, R20.1, TP3.TP, USE.8, USS.8, USW.8, X-SOUTH.10
S_I2C_V: U7.8, X-SOUTH.135
S_REF: R20.2, TP4.TP, U2.1, U2.3, USE.2, USE.5, USS.2, USS.5, USW.2, USW.5
S_SCL: U7.2, X-SOUTH.143
S_SDA: U7.1, X-SOUTH.141
S_VE: X-SOUTH.13, X-SOUTH.19, X-SOUTH.25, X-SOUTH.31, X-SOUTH.37
S_VE_CV: C11.1, R10.1, X-SOUTH.2
S_VE_OV: USE.7, X-SOUTH.1
S_VE_UV: USE.1, X-SOUTH.7
S_VS: C45.1, C46.1, C47.1, C48.1, C49.1, C72.1, C73.1, C74.1, C81.1, C82.1, C83.1, SENSOR.A30, SENSOR.D28, SENSOR.D30, SENSOR.G1, SENSOR.H28, SENSOR.Y21, SENSOR.Z1, SENSOR.Z2, SENSOR.Z3, SENSOR.Z4, TP6.TP, X-SOUTH.49, X-SOUTH.55, X-SOUTH.61, X-SOUTH.67, X-SOUTH.73, X-SOUTH.79, X-SOUTH.85, X-SOUTH.91, X-SOUTH.97
S_VS_CV: C12.1, R13.1, X-SOUTH.4
S_VS_OV: USS.7, X-SOUTH.3
S_VS_UV: USS.1, X-SOUTH.9
S_VW: C90.1, U3.1, U3.3, X-SOUTH.109, X-SOUTH.115, X-SOUTH.121, X-SOUTH.127, X-SOUTH.133
S_VW_CV: C13.1, R16.1, X-SOUTH.6
S_VW_OV: USW.7, X-SOUTH.5
S_VW_UV: USW.1, X-SOUTH.11
TDIG1: SENSOR.G27, SENSOR.Z8, U5.9
TDIG2: SENSOR.G26, SENSOR.Z7, U6.11
T_EXP1: SENSOR.H30, U5.12
T_EXP2: SENSOR.E29, SENSOR.Y24, SENSOR.Z5, SENSOR.Z6, SENSOR.Z13, U6.10
VRAMP1: C16.1, R23.1, SENSOR.G29, SENSOR.Z9
VRAMP2: C17.1, R23.2, SENSOR.F29
VTREF: C65.1, C91.2, R21.2, R24.1, SENSOR.B2, U3.4
VTSIG: C66.1, R24.2, SENSOR.C2

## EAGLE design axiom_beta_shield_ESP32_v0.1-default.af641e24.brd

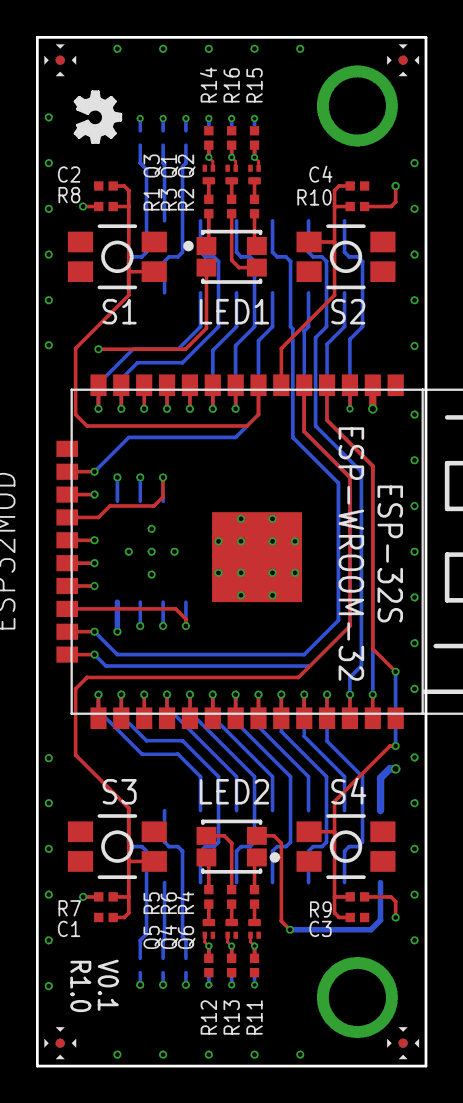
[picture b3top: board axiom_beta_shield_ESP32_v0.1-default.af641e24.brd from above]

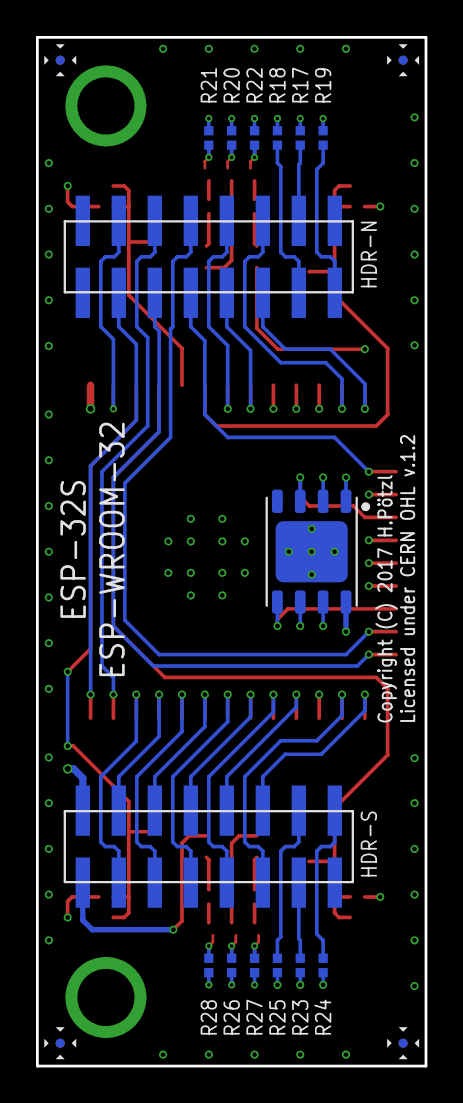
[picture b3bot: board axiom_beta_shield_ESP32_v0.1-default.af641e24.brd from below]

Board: 4 copper layers, 21.6 x 57.1 mm, 49 parts (15 on the bottom side), 61 nets.

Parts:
C1, C2, C3, C4: 0402-C
HDR-N: 2X08M_SMD
HDR-S: 2X08M_SMD
LED1, LED2: RGBLED_PLCC4
LOGO1: OSHW_LOGO_FILLX0100-NT; OSHW_FILLX100_NOTEXT
Q1, Q2, Q3, Q4, Q5, Q6: PMZB290UNE; SOT883(B)
R1, R2, R3, R4, R5, R6, R7, R8, R9, R10, R11, R12, R13, R14, R15, R16, R17, R18, R19, R20, R21, R22, R23, R24, R25, R26, R27, R28: 0402-C
S1, S2, S3, S4: DTSM-6; 3X4MM
U1: ESP32MOD
U$1: IS25LP128; WSON127P600X500-8N

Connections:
B1: Q1.3, R3.1
B2: Q4.3, R6.1
G1: Q2.3, R2.1
G2: Q5.3, R5.1
GND: C1.2, C2.2, C3.2, C4.2, HDR-N.1, HDR-N.2, Q1.2, Q2.2, Q3.2, Q4.2, Q5.2, Q6.2, R11.1, R12.1, R13.1, R14.1, R15.1, R16.1, S1.1, S2.1, S3.1, S4.1, U1.0, U1.1, U1.15, U1.38, U$1.4, U$1.PAD
LED1_B: R20.2, U1.11
LED1_G: R21.2, U1.12
LED1_R: R22.2, U1.10
LED2_R: R28.2, U1.27
unnamed: LED1.1, R1.2
unnamed: LED1.4, R2.2
unnamed: LED1.3, R3.2
unnamed: LED2.1, R4.2
unnamed: LED2.4, R5.2
unnamed: LED2.3, R6.2
unnamed: Q3.1, R14.2, R19.1, R22.1
unnamed: Q2.1, R15.2, R18.1, R21.1
unnamed: Q1.1, R16.2, R17.1, R20.1
unnamed: Q4.1, R13.2, R23.1, R26.1
unnamed: Q5.1, R12.2, R24.1, R27.1
unnamed: Q6.1, R11.2, R25.1, R28.1
R1: Q3.3, R1.1
R2: Q6.3, R4.1
S1: C2.1, R8.1, S1.4, U1.7
S2: C4.1, R10.1, S2.4, U1.6
S3: C1.1, R7.1, S3.4, U1.5
S4: C3.1, R9.1, S4.4, U1.4
SH_N_IO0: HDR-N.12, U1.13
SH_N_IO1: HDR-N.11, U1.14
SH_N_IO2: HDR-N.10, U1.8
SH_N_IO3: HDR-N.9, U1.9
SH_N_IO4: HDR-N.8, U1.23
SH_N_IO5: HDR-N.7, U1.16
SH_N_IO6: HDR-N.6, U1.36
SH_N_IO7: HDR-N.5, U1.24
SH_N_IO8: HDR-N.4, U1.3
SH_N_IO9: HDR-N.3, R27.2, U1.37
SH_S_IO0: HDR-S.12, U1.25
SH_S_IO1: HDR-S.11, U1.26
SH_S_IO2: HDR-S.10, R26.2, U1.28
SH_S_IO3: HDR-S.9, U1.29
SH_S_IO4: HDR-S.8, U1.30
SH_S_IO5: HDR-S.7, U1.31
SH_S_IO6: HDR-S.6, U1.32
SH_S_IO7: HDR-S.5, U1.33
SH_S_IO8: HDR-S.4, U1.34
SH_S_IO9: HDR-S.3, U1.35
SPI: U1.22, U$1.5
SPICLK: U1.20, U$1.6
SPICS0: U1.19, U$1.1
SPIHD: U1.17, U$1.7
SPIQ: U1.21, U$1.2
SPIWP: U1.18, U$1.3
VCC: HDR-S.2, R7.2, R8.2, R9.2, R10.2, U1.2, U$1.8
VDD: HDR-S.1, LED1.2, LED2.2
XX1_N: HDR-N.14, R17.2
XX2_N: HDR-N.13, R18.2
XX2_P: HDR-N.15, R19.2
XX3_P: HDR-S.13, R23.2
XX4_N: HDR-S.16, R24.2
XX4_P: HDR-S.14, R25.2

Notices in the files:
axiom_beta_sensor_cmv12000_v0.9-default.ad180db3.brd:
Copyright (C) 2014 Herbert Poetzl
Licensed under CERN OHL v1.2
axiom_beta_sensor_cmv12000_zif_v0.18_r1.2-default.4a38b4e2.brd:
Copyright (C) 2015 Herbert Pötzl
axiom_beta_shield_ESP32_v0.1-default.af641e24.brd:
Copyright (C) 2017 H.Pötzl
parts and their libraries:
microbuilder: This work is placed in the public domain, and may be freely used for commercial and non-commercial work with the following conditions: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
